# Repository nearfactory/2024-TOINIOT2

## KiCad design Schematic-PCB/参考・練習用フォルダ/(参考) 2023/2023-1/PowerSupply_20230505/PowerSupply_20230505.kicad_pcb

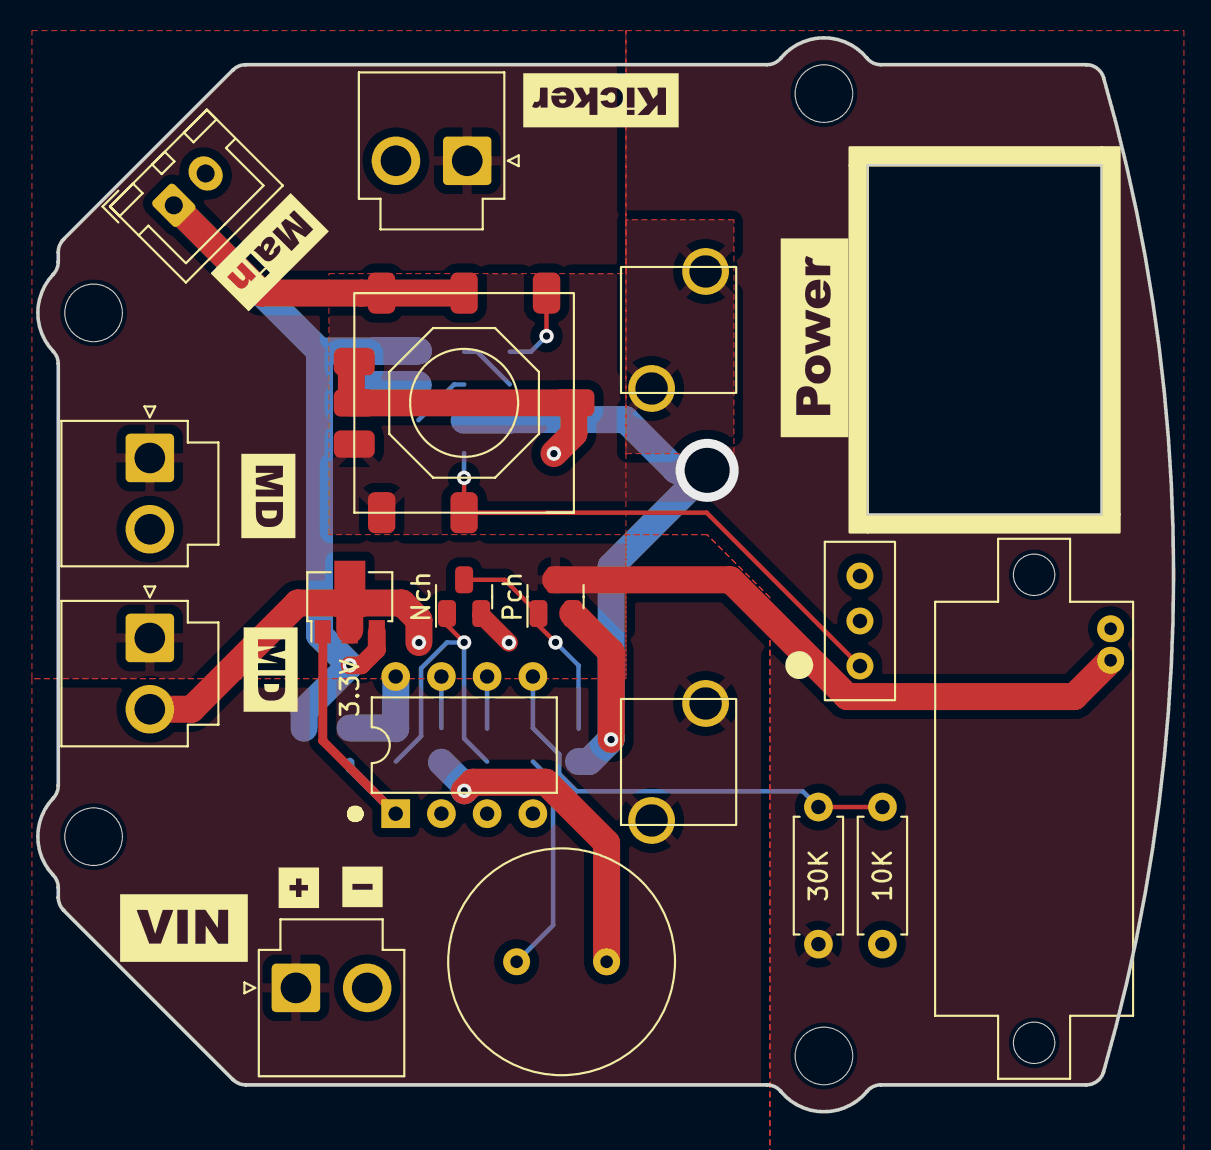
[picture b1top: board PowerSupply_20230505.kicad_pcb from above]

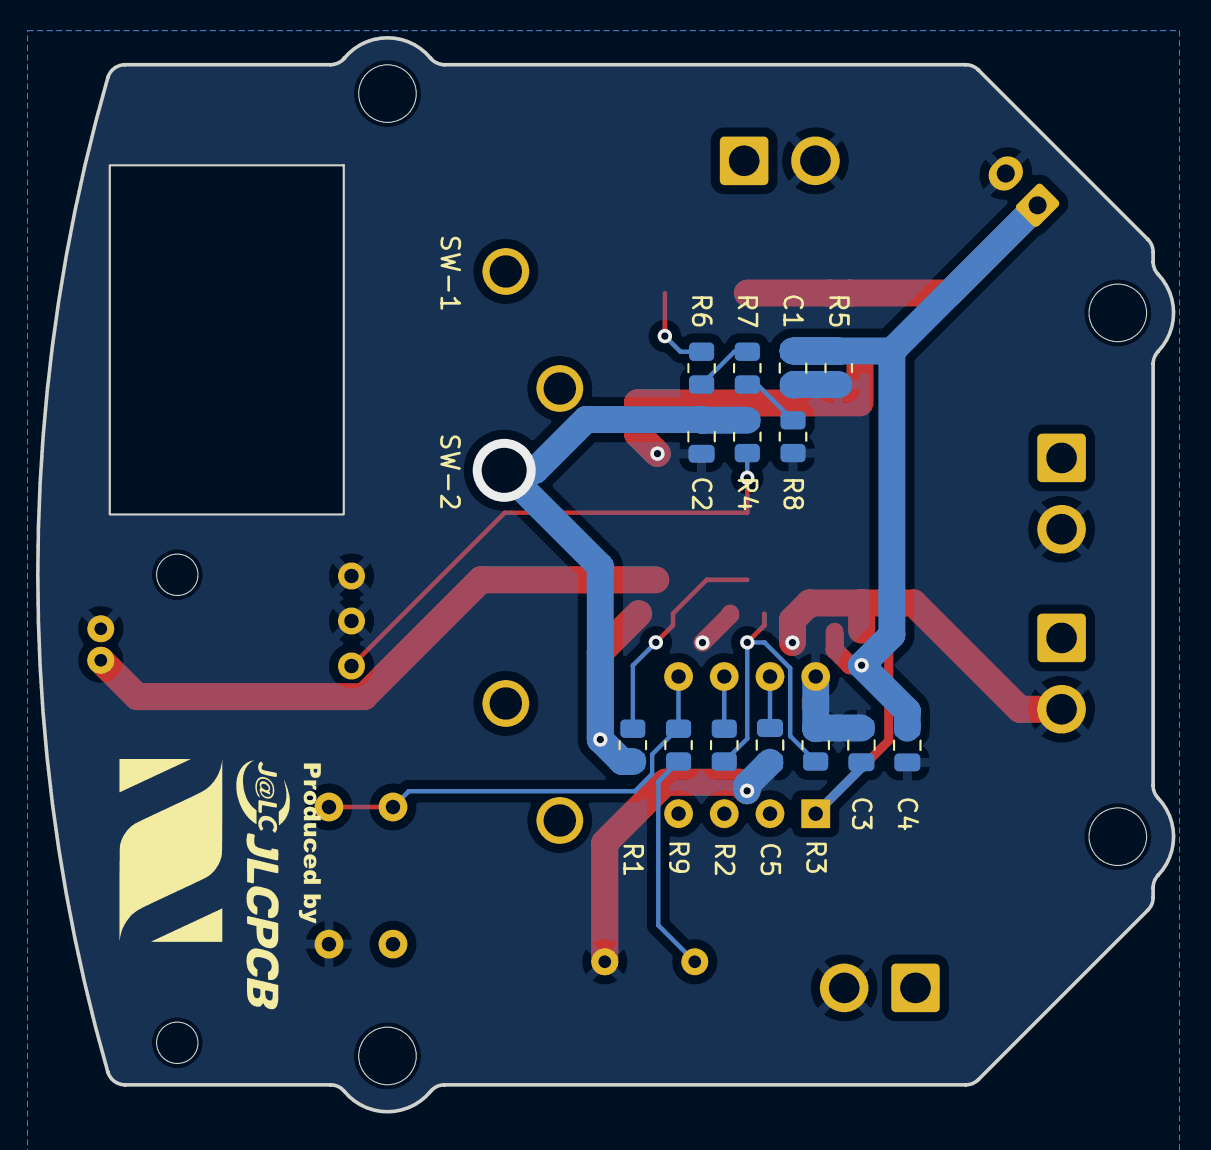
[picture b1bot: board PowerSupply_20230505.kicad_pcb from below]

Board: 2 copper layers, 63.1 x 59.7 mm, 31 parts (14 on the bottom side), 16 nets.

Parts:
3.3V: SOT-89-3
10K: 10K; R_Axial_DIN0207_L6.3mm_D2.5mm_P7.62mm_Horizontal
30K: 30K; R_Axial_DIN0207_L6.3mm_D2.5mm_P7.62mm_Horizontal
BZ1: Buzzer; PKM13EPYH4000-A0
C1: 10µF; C_0805_2012Metric
C2: 22µF; C_0805_2012Metric
C3: 2.2µF; C_0805_2012Metric
C4: 1.0µF; C_0805_2012Metric
C5: 0.1µF; C_0805_2012Metric
F1: Fuse
J1, J2, J4, J5: Conn_01x02_Pin; JST_VH_B2P-VH-B_1x02_P3.96mm_Vertical
J3: Conn_01x02_Pin; JST_XH_B2B-XH-A_1x02_P2.50mm_Vertical
MES1: Voltmeter_DC; VoltMeter
Nch: NMOS; N
Pch: PMOS; P
R1, R3: 10K; R_0805_2012Metric
R2: 100; R_0805_2012Metric
R4: 20k; R_0805_2012Metric
R5: 1.2k; R_0805_2012Metric
R6: 1k; R_0805_2012Metric
R7: 330; R_0805_2012Metric
R8: 10; R_0805_2012Metric
R9: 1K; R_0805_2012Metric
SW1: Locker; RA1113112R
SW2: SW_DPDT_x2; SS12D01G4
U1: OKL-T6-W12N-C
●: PIC12F683-IP; DIP-8_W7.62mm

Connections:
+5V: 3.3V.3 (Vin), C1.1, C4.1, J3.1, R5.2, U1.4 (Vout), U1.5 (Sense)
GND: 3.3V.2 (GND), 10K.2, BZ1.2 (+), C1.2, C2.2, C3.1, C4.2, C5.2, J1.2, J2.2, J3.2, J4.2, J5.2, MES1.1 (-), Nch.3 (S), R3.2, R5.1, R8.2, SW2.2 (B), SW2.3 (C), U1.3 (GND), U1.7 (GND), ●.8 (VSS)
unnamed: BZ1.1 (-), R9.2
unnamed: Nch.2 (D), Pch.2 (G), R1.2
unnamed: Nch.1 (G), R2.1, R3.1
unnamed: R6.2, R7.2
unnamed: R7.1, R8.1
unnamed: R4.2, SW2.1 (A), U1.1 (ON/OFF)
unnamed: R6.1, U1.6 (Trim)
unnamed: 3.3V.1 (Vout), C3.2, ●.1 (VDD)
unnamed: C5.1, ●.7 (GP0)
unnamed: 10K.1, 30K.2, R9.1, ●.5 (GP2)
V_control: R2.2, ●.6 (GP1)
V_raw: F1.1, J1.1
V_raw2: 30K.1, C2.1, Pch.3 (S), R1.1, R4.1, U1.2 (Vin)
Vin: J2.1, J4.1, J5.1, MES1.2 (+), Pch.1 (D)

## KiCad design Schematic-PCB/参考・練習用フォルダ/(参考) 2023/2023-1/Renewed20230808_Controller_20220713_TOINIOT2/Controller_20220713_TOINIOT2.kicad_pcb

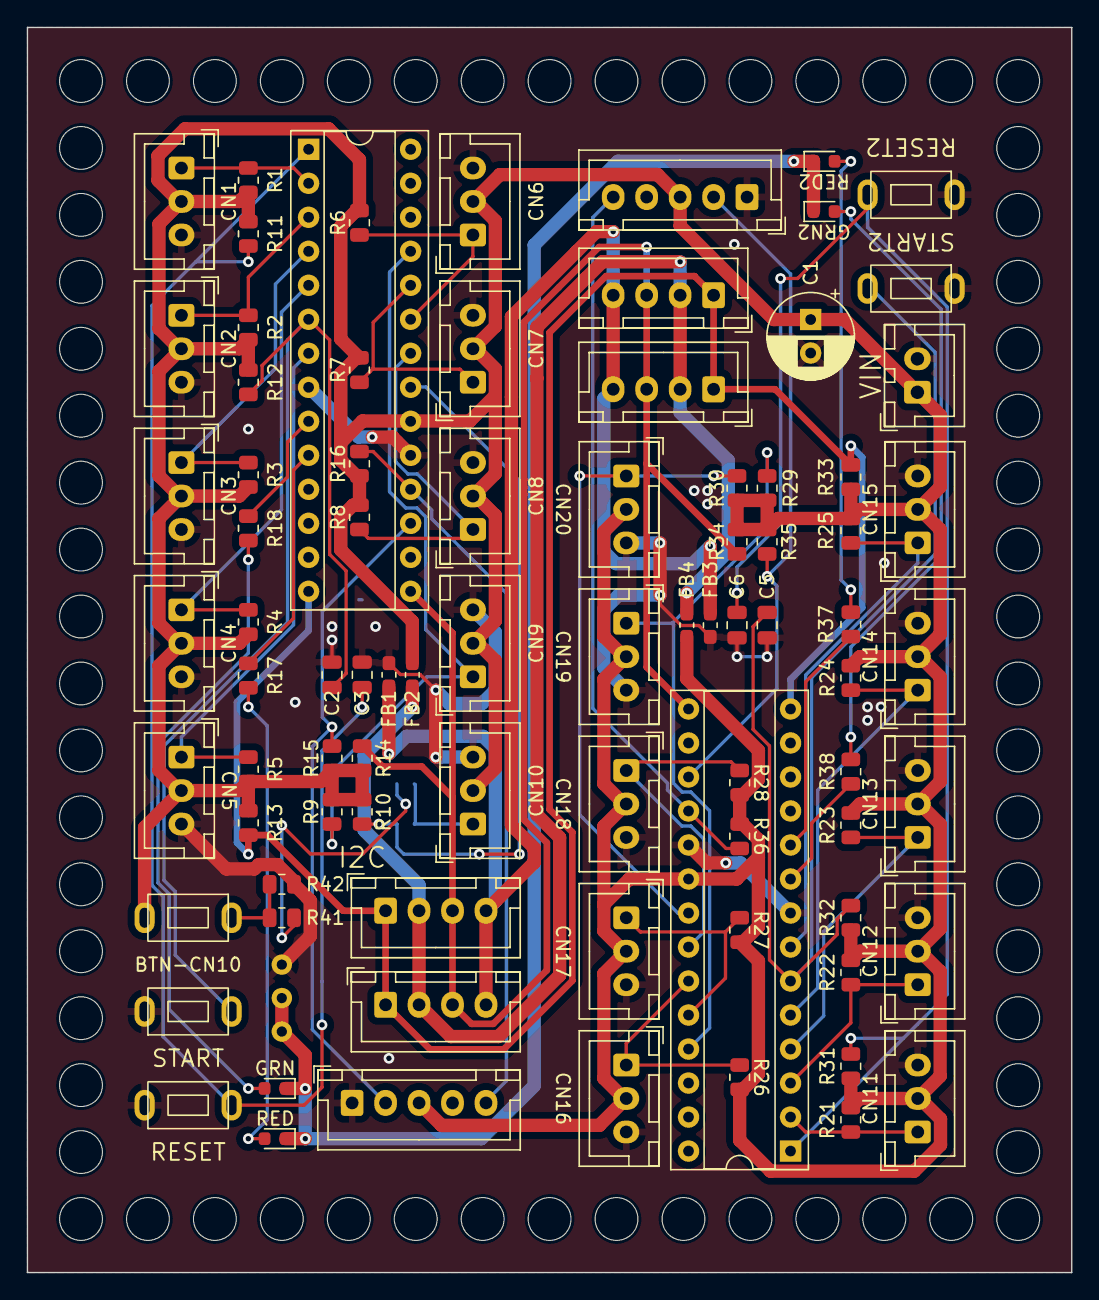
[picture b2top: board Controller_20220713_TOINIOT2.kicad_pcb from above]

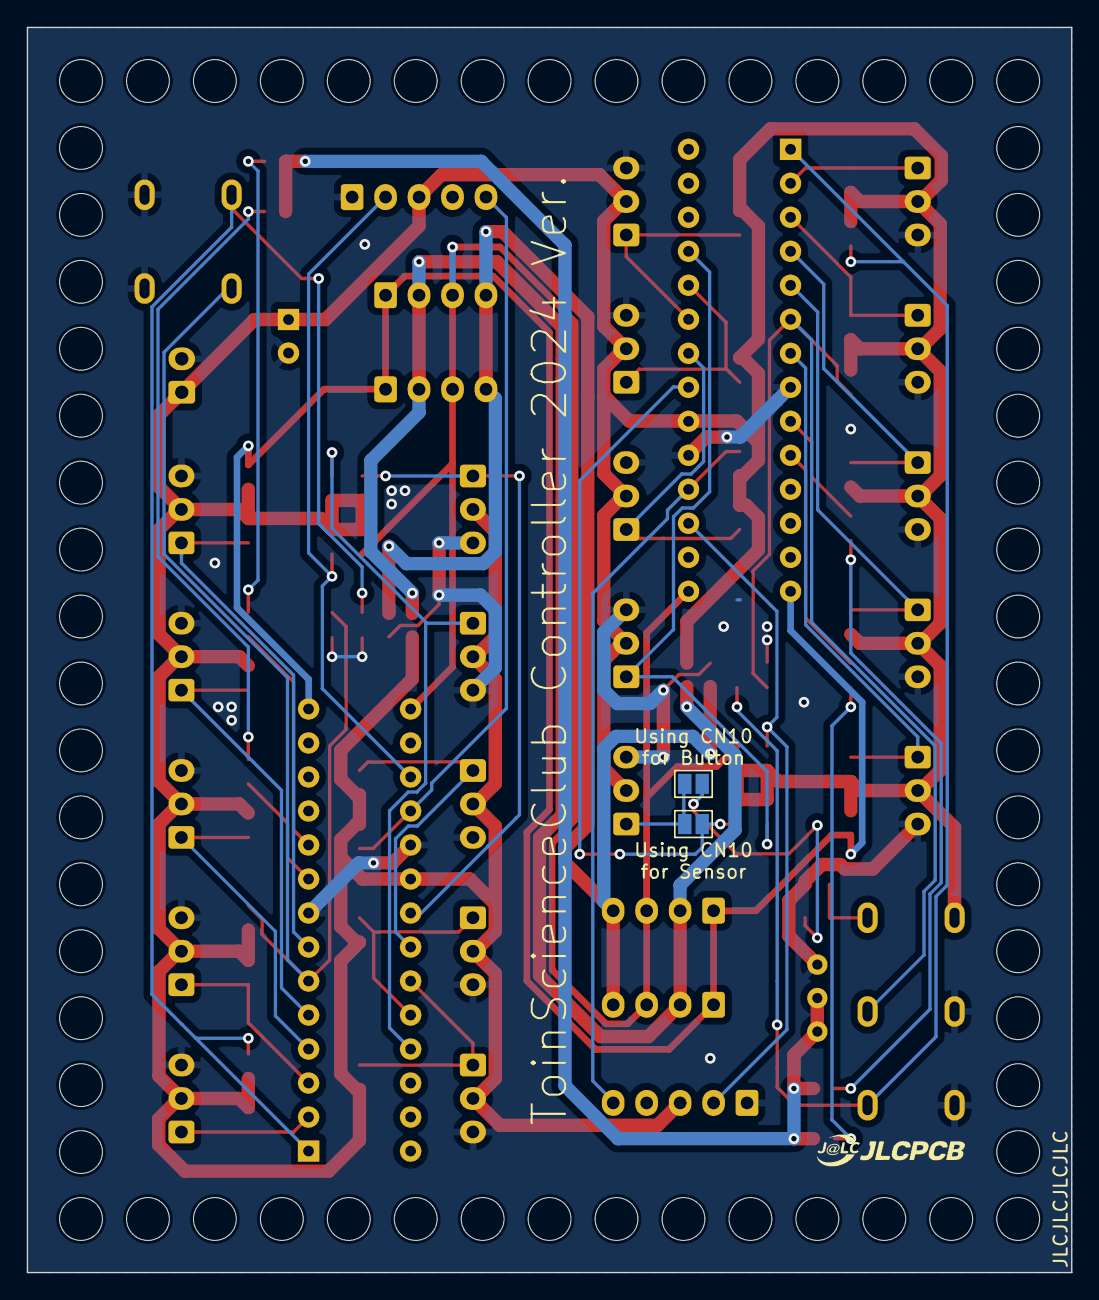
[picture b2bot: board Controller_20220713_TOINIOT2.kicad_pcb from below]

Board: 2 copper layers, 78.0 x 93.0 mm, 88 parts (2 on the bottom side), 46 nets.

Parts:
BTN-CN10: SW_DPST_x2; TVBP06-B043C-B タクトスイッチ小
C1: C; CP_Radial_D6.3mm_P2.50mm
C2, C3, C5, C6: C; C_0805_2012Metric
CN1, CN2, CN3, CN4, CN5, CN6, CN7, CN8, CN9, CN10, CN11, CN12, CN13, CN14, CN15, CN16, CN17, CN18, CN19, CN20: Conn_01x03_Male; JST_XH_B3B-XH-A_1x03_P2.50mm_Vertical
FB1, FB2, FB3, FB4: FerriteBead; L_0603_1608Metric_Pad1.05x0.95mm_HandSolder
GRN, GRN2: LED; LED_0603_1608Metric
I2C1, I2C2, I2C3, I2C4: Conn_01x04_Male; JST_XH_B4B-XH-A_1x04_P2.50mm_Vertical
J1: Conn_01x02_Male; JST_XH_B2B-XH-A_1x02_P2.50mm_Vertical
JP1, JP2: Jumper_2_Open; SolderJumper-2_P1.3mm_Open_Pad1.0x1.5mm
R1, R2, R3, R4, R5, R6, R7, R8, R9, R10, R21, R22, R23, R24, R25, R26, R27, R28, R29, R30: 100kR; R_0805_2012Metric
R11, R12, R13, R14, R15, R16, R31, R32, R33, R34, R35, R36: 10kR; R_0805_2012Metric
R17, R18: 330Ω; R_0805_2012Metric
R37: 150Ω; R_0805_2012Metric
R38: 470Ω; R_0805_2012Metric
R41: 1K; R_0805_2012Metric
R42: 10K; R_0805_2012Metric
RED, RED2: LED; LED_0603_1608Metric
RESET, RESET2: DTS62K; TVBP06-B043C-B タクトスイッチ小
SER1, SER2: Conn_01x05_Male; JST_XH_B5B-XH-A_1x05_P2.50mm_Vertical
START, START2: DTS25N; TVBP06-B043C-B タクトスイッチ小
SW5: SW_DPDT_x2; SS12D01G4 スライドスイッチ
U1, U2: PIC18F2620; DIP-28_W7.62mm_Socket

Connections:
+5V: BTN-CN10.1 (A), C1.1, CN1.2, CN2.2, CN3.2, CN4.2, CN5.2, CN6.2, CN7.2, CN8.2, CN9.2, CN10.2, CN11.2, CN12.2, CN13.2, CN14.2, CN15.2, CN16.2, CN17.2, CN18.2, CN19.2, CN20.2, FB2.1, FB4.1, J1.1, R1.1, R2.1, R3.1, R4.1, R5.1, R6.1, R7.1, R8.1, R9.1, R10.1, R11.1, R12.1, R13.1, R14.1, R15.1, R16.1, R21.1, R22.1, R23.1, R24.1, R25.1, R26.1, R27.1, R28.1, R29.1, R30.1, R31.1, R32.1, R33.1, R34.1, R35.1, R36.1, SER1.3, SER2.3, U1.20 (VDD), U2.20 (VDD)
+5V_I2C: FB2.2, FB4.2, I2C1.2, I2C2.2, I2C3.2, I2C4.2
AD1: CN1.1, R1.2, U1.2 (AD1)
AD1_2: CN11.1, R21.2, U2.2 (AD1)
AD2: CN2.1, R2.2, U1.3 (AD2)
AD2_2: CN12.1, R22.2, U2.3 (AD2)
AD3: CN3.1, R3.2, U1.4 (AD3)
AD3_2: CN13.1, R23.2, U2.4 (AD3)
AD4: CN4.1, R4.2, U1.5 (AD4)
AD4_2: CN14.1, R24.2, U2.5 (AD4)
AD5: CN5.1, R5.2, U1.7 (AD5)
AD5_2: CN15.1, R25.2, U2.7 (AD5)
AD6: CN6.1, R6.2, U1.23 (AD6)
AD6_2: CN16.1, R26.2, U2.23 (AD6)
AD7: CN7.1, R7.2, U1.24 (AD7)
AD7_2: CN17.1, R27.2, U2.24 (AD7)
AD8: CN8.1, R8.2, U1.22 (AD8)
AD8_2: CN18.1, R28.2, U2.22 (AD8)
AD9: CN9.1, R9.2, U1.25 (AD9)
AD9_2: CN19.1, R29.2, U2.25 (AD9)
AD10: JP1.1 (A), R10.2, U1.21 (AD10)
AD10_2: CN20.1, R30.2, U2.21 (AD10)
AD10_BTN: JP2.2 (B), R41.2
GND: C1.2, C2.2, C3.2, C5.2, C6.2, CN1.3, CN2.3, CN3.3, CN4.3, CN5.3, CN6.3, CN7.3, CN8.3, CN9.3, CN10.3, CN11.3, CN12.3, CN13.3, CN14.3, CN15.3, CN16.3, CN17.3, CN18.3, CN19.3, CN20.3, FB1.1, FB3.1, J1.2, R42.1, RESET.2, RESET2.2, SER1.1, SER2.1, START.2, START2.2, SW5.1 (A), U1.8 (GND), U1.19 (VSS), U2.8 (GND), U2.19 (VSS)
GND_I2C: FB1.2, FB3.2, I2C1.4, I2C2.4, I2C3.4, I2C4.4
LED_GND: GRN.1 (K), GRN2.1 (K), RED.1 (K), RED2.1 (K), SW5.2 (B), SW5.3 (C)
MCLR: C3.1, R11.2, RESET.1, U1.1 (MCLR)
MCLR_2: C6.1, R31.2, RESET2.1, U2.1 (MCLR)
MON_LED: R17.2, U1.10 (MON_LED)
MON_LED_2: R37.2, U2.10 (MON_LED)
unnamed: CN10.1, JP1.2 (B), JP2.1 (A)
unnamed: GRN.2 (A), R18.1
unnamed: GRN2.2 (A), R38.1
unnamed: R17.1, RED.2 (A)
unnamed: R37.1, RED2.2 (A)
unnamed: BTN-CN10.2 (B), R41.1, R42.2
PWR_LED: R18.2, U1.9 (PWR_LED)
PWR_LED_2: R38.2, U2.9 (PWR_LED)
RA4: C2.1, R12.2, START.1, U1.6 (RA4)
RA4_2: C5.1, R32.2, START2.1, U2.6 (RA4)
RX: R16.2, SER1.5, U1.18 (RX)
RX_2: R36.2, SER2.5, U2.18 (RX)
SCL: I2C1.1, I2C2.1, I2C3.1, I2C4.1, R13.2, R33.2, U1.14 (SCL), U2.14 (SCL)
SDA: I2C1.3, I2C2.3, I2C3.3, I2C4.3, R14.2, R34.2, U1.15 (SDA), U2.15 (SDA)
TX: R15.2, SER1.2, U1.17 (TX)
TX_2: R35.2, SER2.2, U2.17 (TX)

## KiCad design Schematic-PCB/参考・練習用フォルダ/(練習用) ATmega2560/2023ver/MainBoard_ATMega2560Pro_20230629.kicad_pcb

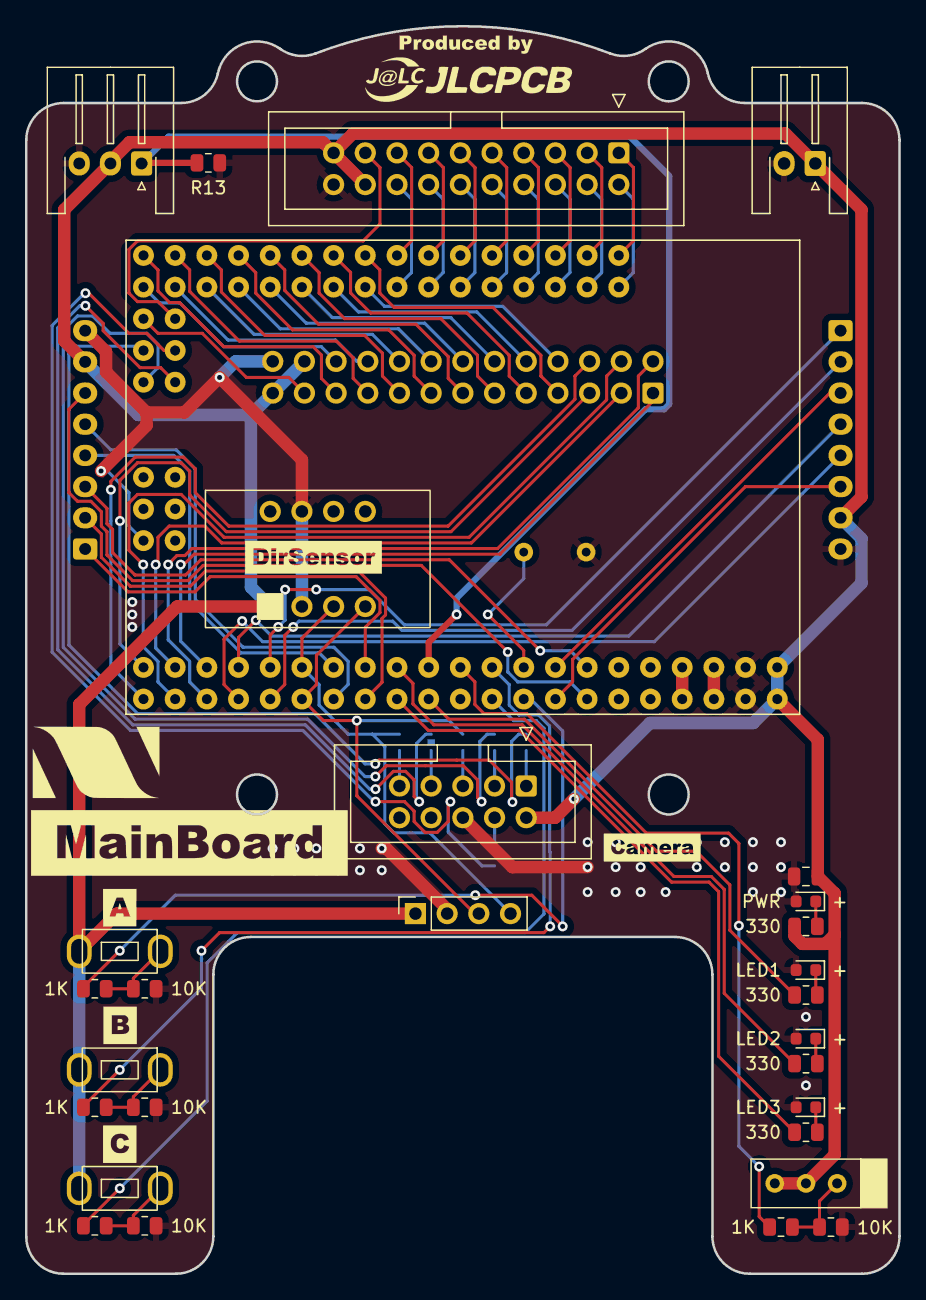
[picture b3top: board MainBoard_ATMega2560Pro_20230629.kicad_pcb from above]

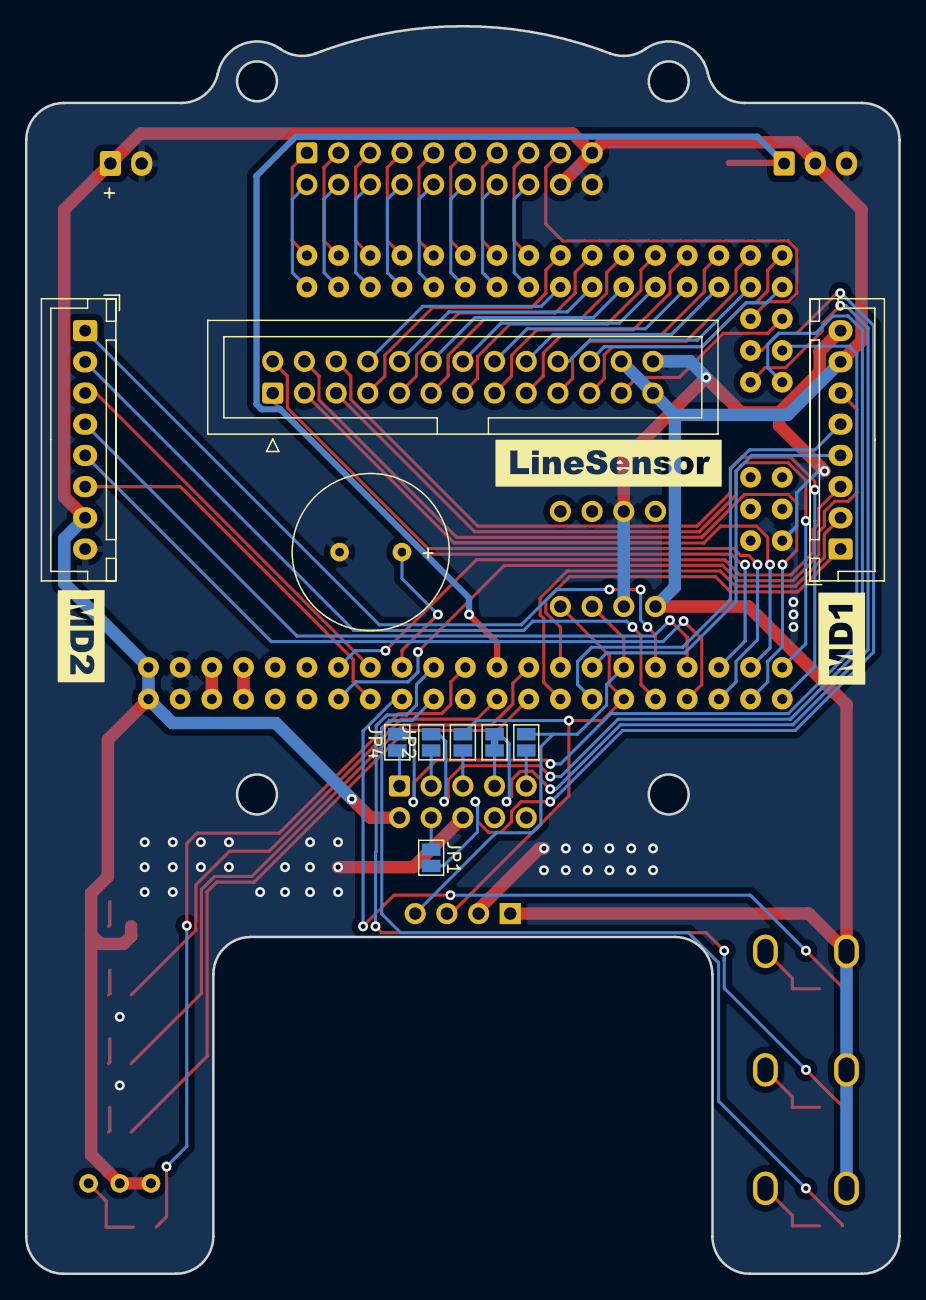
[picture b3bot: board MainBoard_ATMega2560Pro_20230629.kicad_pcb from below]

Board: 2 copper layers, 70.0 x 100.0 mm, 39 parts (10 on the bottom side), 83 nets.

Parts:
BZ1: Buzzer; PKM13EPYH4000-A0
C1: C; C_0805_2012Metric
J1: Conn_01x10_Pin; IDC-Header_2x05_P2.54mm_Vertical
J2, J4: Conn_01x08_Male; JST_XH_B8B-XH-A_1x08_P2.50mm_Vertical
J3: Conn_01x04_Female; PinSocket_1x04_P2.54mm_Vertical
J5: Conn_01x02_Male; JST_XH_S2B-XH-A-1_1x02_P2.50mm_Horizontal
J6: Conn_01x20_Male; IDC-Header_2x10_P2.54mm_Vertical
J7: Conn_01x26_Male; IDC-Header_2x13_P2.54mm_Vertical
J8: Conn_01x03_Pin; JST_XH_S3B-XH-A-1_1x03_P2.50mm_Horizontal
JP1, JP2, JP4, JP5, JP6: Jumper_2_Open; SolderJumper-2_P1.3mm_Open_Pad1.0x1.5mm
JP3: Jumper_2_Bridged; SolderJumper-2_P1.3mm_Bridged_Pad1.0x1.5mm
LED1, LED2, LED3: LED; LED_0603_1608Metric
PWR: LED; LED_0603_1608Metric
R1, R2, R3, R4: 330; R_0805_2012Metric
R5, R7, R9, R11, R13: 1K; R_0805_2012Metric
R6, R8, R10, R12: 10K; R_0805_2012Metric
SW1, SW2, SW3: SW_DPST_x2; TVBP06-B043C
SW4: SW_DPDT_x2; SS12D01G4
U1: ATMEGA2560_pro; MODULE_MEGA_PRO_EMBED_CH340G___ATMEGA2560
U2: BNO055

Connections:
GND: BZ1.2 (+), C1.2, J1.6, J2.8, J3.2, J4.8, J5.2, J6.20, J7.26, J8.3, LED1.2 (A), LED2.2 (A), LED3.2 (A), PWR.2 (A), R6.1, R8.1, R10.1, R12.1, R13.2, U1.GND_1 (GND), U1.GND_2 (GND), U1.GND_3 (GND), U2.2 (GND), U2.7 (GND)
MISO: JP4.2 (B), U1.D50
MOSI: JP1.2 (B), U1.D51
unnamed: PWR.1 (K), R1.2
unnamed: LED1.1 (K), R2.2
unnamed: LED2.1 (K), R3.2
unnamed: LED3.1 (K), R4.2
unnamed: J1.1, JP4.1 (A)
unnamed: J1.3, JP2.1 (A)
unnamed: J1.4, JP1.1 (A)
unnamed: J1.5, JP5.1 (A)
unnamed: J1.7, JP3.1 (A)
unnamed: J1.9, JP6.1 (A)
unnamed: R5.1, R6.2, SW1.2 (B)
unnamed: R7.1, R8.2, SW2.2 (B)
unnamed: R9.1, R10.2, SW3.2 (B)
unnamed: R11.1, R12.2, SW4.3 (C)
PWM_Buzzer: BZ1.1 (-), U1.D6
PWM_M1: J2.3, U1.D2
PWM_M2: J2.6, U1.D3
PWM_M3: J4.3, U1.D4
PWM_M4: J4.6, U1.D5
SCK: JP2.2 (B), U1.D52
SCL: J3.3, JP5.2 (B), U1.D21, U2.4 (SCL/R)
SDA: J3.4, JP6.2 (B), U1.D20, U2.3 (SDA/T)
SS: JP3.2 (B), U1.D53
Sig1_BALL: J6.1, U1.A0
Sig1_LINE: J7.1, U1.D26
Sig2_BALL: J6.2, U1.A1
Sig2_LINE: J7.2, U1.D27
Sig3_BALL: J6.3, U1.A2
Sig3_LINE: J7.3, U1.D28
Sig4_BALL: J6.4, U1.A3
Sig4_LINE: J7.4, U1.D29
Sig5_BALL: J6.5, U1.A4
Sig5_LINE: J7.5, U1.D30
Sig6_BALL: J6.6, U1.A5
Sig6_LINE: J7.6, U1.D31
Sig7_BALL: J6.7, U1.A6
Sig7_LINE: J7.7, U1.D32
Sig8_BALL: J6.8, U1.A7
Sig8_LINE: J7.8, U1.D33
Sig9_BALL: J6.9, U1.A8
Sig9_LINE: J7.9, U1.D34
Sig10_BALL: J6.10, U1.A9
Sig10_LINE: J7.10, U1.D35
Sig11_BALL: J6.11, U1.A10
Sig11_LINE: J7.11, U1.D36
Sig12_BALL: J6.12, U1.A11
Sig12_LINE: J7.12, U1.D37
Sig13_BALL: J6.13, U1.A12
Sig13_LINE: J7.13, U1.D38
Sig14_BALL: J6.14, U1.A13
Sig14_LINE: J7.14, U1.D39
Sig15_BALL: J6.15, U1.A14
Sig15_LINE: J7.15, U1.D40
Sig16_BALL: J6.16, U1.A15
Sig16_LINE: J7.16, U1.D41
Sig17_LINE: J7.17, U1.D42
Sig18_LINE: J7.18, U1.D43
Sig19_LINE: J7.19, U1.D44
Sig20_LINE: J7.20, U1.D45
Sig21_LINE: J7.21, U1.D46
Sig22_LINE: J7.22, U1.D47
Sig23_BALL-Kicker: J7.23, U1.D48
Sig_BTN1: R5.2, U1.D7
Sig_BTN2: R7.2, U1.D8
Sig_BTN3: R9.2, U1.D9
Sig_Kicker: J8.1, R13.1, U1.D12
Sig_LED1: R2.1, U1.D13
Sig_LED2: R3.1, U1.D14
Sig_LED3: R4.1, U1.D15
Sig_LEVER: R11.2, U1.D10
Sig_M1-1: J2.1, U1.D16
Sig_M1-2: J2.2, U1.D17
Sig_M2-1: J2.4, U1.D18
Sig_M2-2: J2.5, U1.D19
Sig_M3-1: J4.1, U1.D22
Sig_M3-2: J4.2, U1.D23
Sig_M4-1: J4.4, U1.D24
Sig_M4-2: J4.5, U1.D25
Sig_NeoPixel: J6.17, U1.D49
VIN: C1.1, J1.2, J2.7, J3.1, J4.7, J5.1, J6.18, J6.19, J7.24, J7.25, J8.2, R1.1, SW1.1 (A), SW2.1 (A), SW3.1 (A), SW4.1 (A), SW4.2 (B), U1.VIN_1 (VIN), U1.VIN_2 (VIN), U2.1 (VIN)
